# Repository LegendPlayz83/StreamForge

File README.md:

# StreamForge
This is my keyboard design, which I made from scratch in KiCad and Fusion 360

Features:

- 108x Diodes
- 108x keys
- Raspberry Pi Pico
- Customised layout
- KMK firmware
  
### Schematic

### PCB 

### Case

### BOM

| Name | Quantity | Cost | Link |
|------|----------|------|------|
| Akko Creamy Cyan | 108 | $30 | [Buy](https://stackskb.com/store/akko-creamy-cyan-switch-pack-of-45-pre-order/) |
| Durock Smokey Screw-In Stabilizers V2 (4+1 w/ 6.25u spacebar) | 1 | $18.58 | [Buy](https://stackskb.com/store/durock-smokey-screw-in-stabilizers-v2/) |
| Womier Azure Eclipse Side Backlit Cherry PBT Keycap | 1 | $27 | [Buy](https://curiositycaps.in/products/flow-backlit-side-printed-cherry-pbt-keycap-set) |
| Diode 1N4148 Through-Hole | 100 | $2.15 | [Buy](https://www.amazon.in/dp/B084ZP5BJ3) |
| PCB - (Black Color) | 5 | $66 | [Buy](https://order.lioncircuits.com/) |
| Raspberry Pi Pico | 1 | $7.40 | [Buy](https://amzn.in/d/0dd5MeUx) |
| Heatset and Screws | 1 | $0.00 | Amazon |
| Case (top, mid, bot) | 1 | $0.00 | Printing Legion |
| **Total** | | **$151.13** | |

The total costs come out to be $152

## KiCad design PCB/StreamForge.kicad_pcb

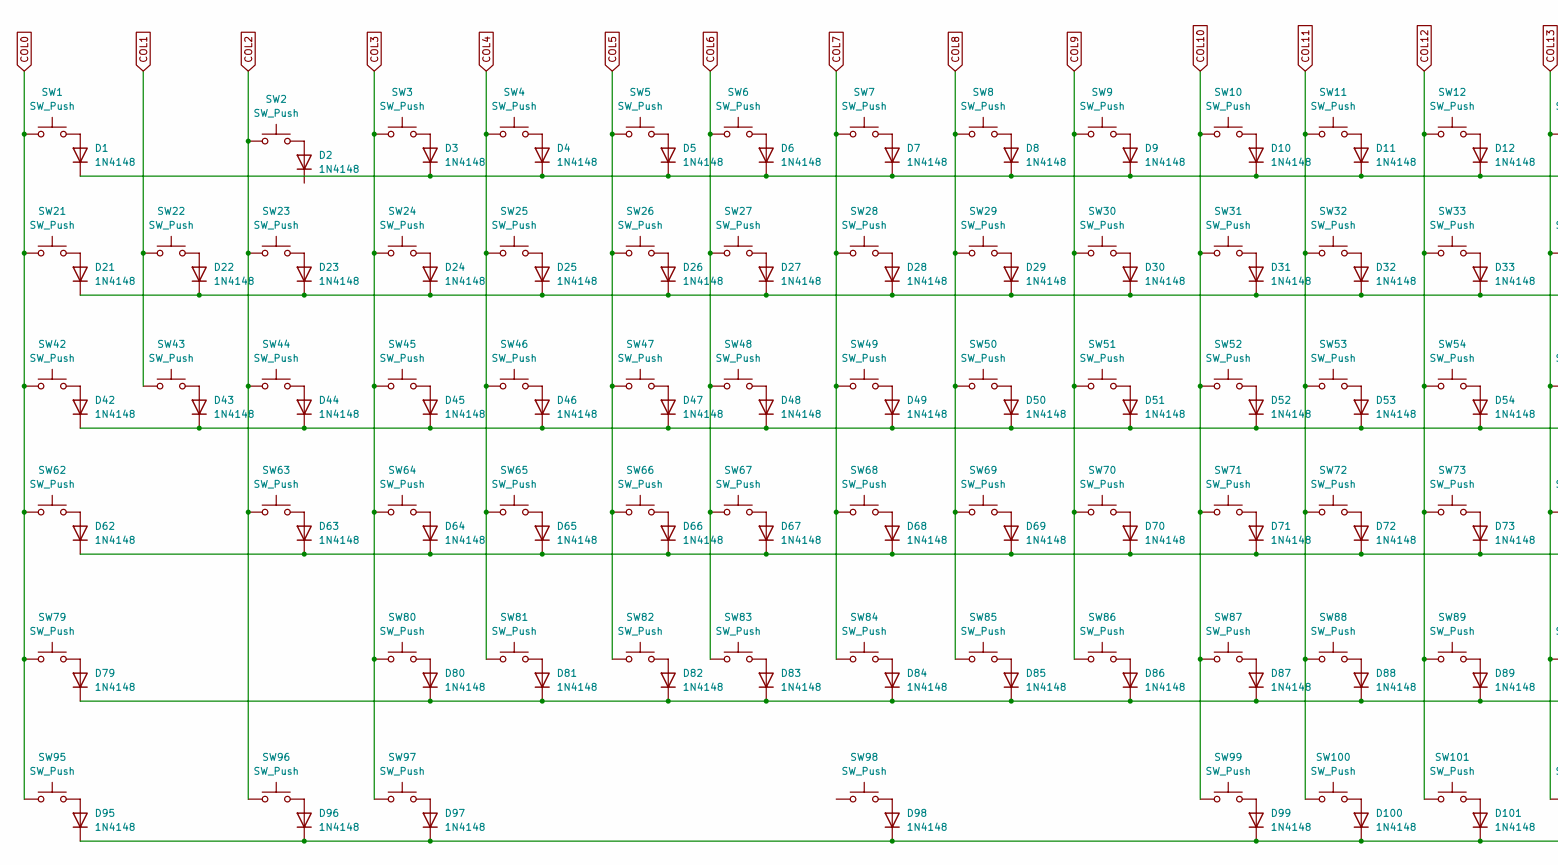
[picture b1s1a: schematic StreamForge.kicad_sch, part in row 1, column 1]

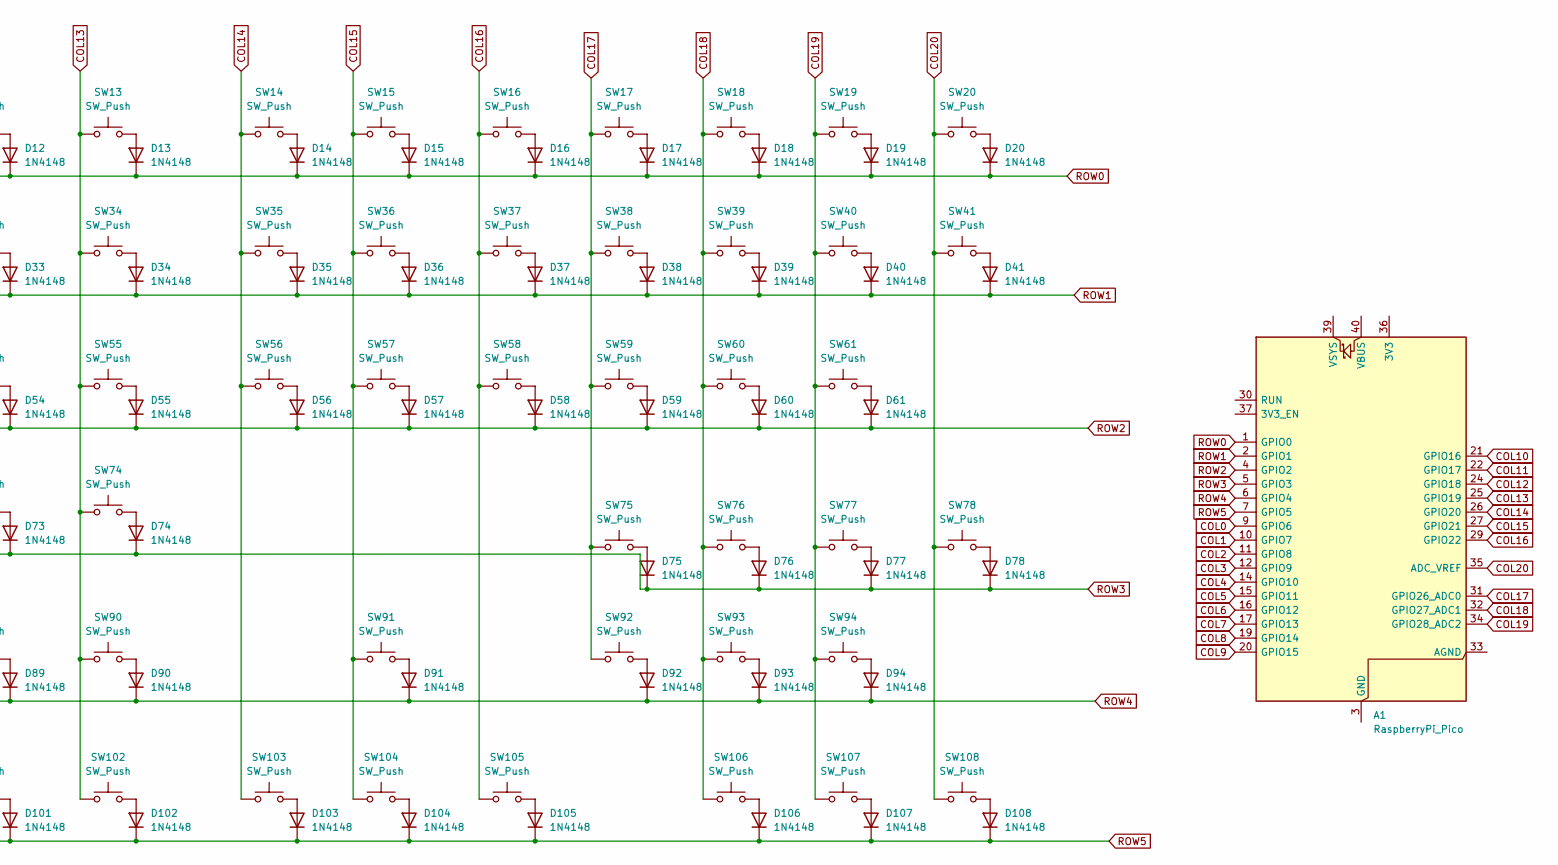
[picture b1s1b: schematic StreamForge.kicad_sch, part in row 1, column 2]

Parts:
A1: RaspberryPi_Pico; RaspberryPi_Pico_Common_THT
D1, D2, D3, D4, D5, D6, D7, D8, D9, D10, D11, D12, D13, D14, D15, D16, D17, D18, D19, D20, D21, D22, D23, D24, D25, D26, D27, D28, D29, D30, D31, D32, D33, D34, D35, D36, D37, D38, D39, D40, D41, D42, D43, D44, D45, D46, D47, D48, D49, D50, D51, D52, D53, D54, D55, D56, D57, D58, D59, D60, D61, D62, D63, D64, D65, D66, D67, D68, D69, D70, D71, D72, D73, D74, D75, D76, D77, D78, D79, D80, D81, D82, D83, D84, D85, D86, D87, D88, D89, D90, D91, D92, D93, D94, D95, D96, D97, D98, D99, D100, D101, D102, D103, D104, D105, D106, D107, D108: 1N4148; D_DO-35_SOD27_P7.62mm_Horizontal
SW1, SW2, SW3, SW4, SW5, SW6, SW7, SW8, SW9, SW10, SW11, SW12, SW13, SW14, SW15, SW16, SW17, SW18, SW19, SW20, SW21, SW22, SW23, SW24, SW25, SW26, SW27, SW28, SW29, SW30, SW31, SW32, SW33, SW35, SW36, SW37, SW38, SW39, SW40, SW41, SW42, SW43, SW44, SW45, SW46, SW47, SW48, SW49, SW50, SW51, SW52, SW53, SW54, SW55, SW56, SW57, SW58, SW59, SW60, SW61, SW62, SW63, SW64, SW65, SW66, SW67, SW68, SW69, SW70, SW71, SW72, SW73, SW75, SW76, SW77, SW79, SW80, SW81, SW82, SW83, SW84, SW85, SW86, SW87, SW88, SW89, SW90, SW91, SW92, SW93, SW94, SW103, SW104, SW105, SW107: SW_Push; SW_Cherry_MX_1.00u_PCB
SW34, SW74, SW106: SW_Push; SW_Cherry_MX_2.00u_PCB
SW78, SW108: SW_Push; SW_Cherry_MX_2.00u_Vertical_PCB
SW95, SW96, SW97, SW99, SW100, SW101, SW102: SW_Push; SW_Cherry_MX_1.25u_PCB
SW98: SW_Push; SW_Cherry_MX_6.25u_PCB

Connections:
COL0: A1.9 (GPIO6), SW1.1, SW21.1, SW42.1, SW62.1, SW79.1, SW95.1
COL1: A1.10 (GPIO7), SW22.1, SW43.1
COL2: A1.11 (GPIO8), SW2.1, SW23.1, SW44.1, SW63.1, SW96.1
COL3: A1.12 (GPIO9), SW3.1, SW24.1, SW45.1, SW64.1, SW80.1, SW97.1
COL4: A1.14 (GPIO10), SW4.1, SW25.1, SW46.1, SW65.1, SW81.1
COL5: A1.15 (GPIO11), SW5.1, SW26.1, SW47.1, SW66.1, SW82.1
COL6: A1.16 (GPIO12), SW6.1, SW27.1, SW48.1, SW67.1, SW83.1
COL7: A1.17 (GPIO13), SW7.1, SW28.1, SW49.1, SW68.1, SW84.1
COL8: A1.19 (GPIO14), SW8.1, SW29.1, SW50.1, SW69.1, SW85.1
COL9: A1.20 (GPIO15), SW9.1, SW30.1, SW51.1, SW70.1, SW86.1
COL10: A1.21 (GPIO16), SW10.1, SW31.1, SW52.1, SW71.1, SW87.1, SW99.1
COL11: A1.22 (GPIO17), SW11.1, SW32.1, SW53.1, SW72.1, SW88.1, SW100.1
COL12: A1.24 (GPIO18), SW12.1, SW33.1, SW54.1, SW73.1, SW89.1, SW101.1
COL13: A1.25 (GPIO19), SW13.1, SW34.1, SW55.1, SW74.1, SW90.1, SW102.1
COL14: A1.26 (GPIO20), SW14.1, SW35.1, SW56.1, SW103.1
COL15: A1.27 (GPIO21), SW15.1, SW36.1, SW57.1, SW91.1, SW104.1
COL16: A1.29 (GPIO22), SW16.1, SW37.1, SW58.1, SW105.1
COL17: A1.31 (GPIO26_ADC0), SW17.1, SW38.1, SW59.1, SW75.1, SW92.1
COL18: A1.32 (GPIO27_ADC1), SW18.1, SW39.1, SW60.1, SW76.1, SW93.1, SW106.1
COL19: A1.34 (GPIO28_ADC2), SW19.1, SW40.1, SW61.1, SW77.1, SW94.1, SW107.1
COL20: A1.35 (ADC_VREF), SW20.1, SW41.1, SW78.1, SW108.1
unnamed: A1.3 (GND), A1.8 (GND), A1.13 (GND), A1.18 (GND), A1.23 (GND), A1.28 (GND), A1.38 (GND)
unnamed: D1.2 (A), SW1.2
unnamed: D2.2 (A), SW2.2
unnamed: D3.2 (A), SW3.2
unnamed: D4.2 (A), SW4.2
unnamed: D5.2 (A), SW5.2
unnamed: D6.2 (A), SW6.2
unnamed: D7.2 (A), SW7.2
unnamed: D8.2 (A), SW8.2
unnamed: D9.2 (A), SW9.2
unnamed: D10.2 (A), SW10.2
unnamed: D11.2 (A), SW11.2
unnamed: D12.2 (A), SW12.2
unnamed: D13.2 (A), SW13.2
unnamed: D14.2 (A), SW14.2
unnamed: D15.2 (A), SW15.2
unnamed: D16.2 (A), SW16.2
unnamed: D17.2 (A), SW17.2
unnamed: D18.2 (A), SW18.2
unnamed: D19.2 (A), SW19.2
unnamed: D20.2 (A), SW20.2
unnamed: D21.2 (A), SW21.2
unnamed: D22.2 (A), SW22.2
unnamed: D23.2 (A), SW23.2
unnamed: D24.2 (A), SW24.2
unnamed: D25.2 (A), SW25.2
unnamed: D26.2 (A), SW26.2
unnamed: D27.2 (A), SW27.2
unnamed: D28.2 (A), SW28.2
unnamed: D29.2 (A), SW29.2
unnamed: D30.2 (A), SW30.2
unnamed: D31.2 (A), SW31.2
unnamed: D32.2 (A), SW32.2
unnamed: D33.2 (A), SW33.2
unnamed: D34.2 (A), SW34.2
unnamed: D35.2 (A), SW35.2
unnamed: D36.2 (A), SW36.2
unnamed: D37.2 (A), SW37.2
unnamed: D38.2 (A), SW38.2
unnamed: D39.2 (A), SW39.2
unnamed: D40.2 (A), SW40.2
unnamed: D41.2 (A), SW41.2
unnamed: D42.2 (A), SW42.2
unnamed: D43.2 (A), SW43.2
unnamed: D44.2 (A), SW44.2
unnamed: D45.2 (A), SW45.2
unnamed: D46.2 (A), SW46.2
unnamed: D47.2 (A), SW47.2
unnamed: D48.2 (A), SW48.2
unnamed: D49.2 (A), SW49.2
unnamed: D50.2 (A), SW50.2
unnamed: D51.2 (A), SW51.2
unnamed: D52.2 (A), SW52.2
unnamed: D53.2 (A), SW53.2
unnamed: D54.2 (A), SW54.2
unnamed: D55.2 (A), SW55.2
unnamed: D56.2 (A), SW56.2
unnamed: D57.2 (A), SW57.2
unnamed: D58.2 (A), SW58.2
unnamed: D59.2 (A), SW59.2
unnamed: D60.2 (A), SW60.2
unnamed: D61.2 (A), SW61.2
unnamed: D62.2 (A), SW62.2
unnamed: D63.2 (A), SW63.2
unnamed: D64.2 (A), SW64.2
unnamed: D65.2 (A), SW65.2
unnamed: D66.2 (A), SW66.2
unnamed: D67.2 (A), SW67.2
unnamed: D68.2 (A), SW68.2
unnamed: D69.2 (A), SW69.2
unnamed: D70.2 (A), SW70.2
unnamed: D71.2 (A), SW71.2
unnamed: D72.2 (A), SW72.2
unnamed: D73.2 (A), SW73.2
unnamed: D74.2 (A), SW74.2
unnamed: D75.2 (A), SW75.2
unnamed: D76.2 (A), SW76.2
unnamed: D77.2 (A), SW77.2
unnamed: D78.2 (A), SW78.2
unnamed: D79.2 (A), SW79.2
unnamed: D80.2 (A), SW80.2
unnamed: D81.2 (A), SW81.2
unnamed: D82.2 (A), SW82.2
unnamed: D83.2 (A), SW83.2
unnamed: D84.2 (A), SW84.2
unnamed: D85.2 (A), SW85.2
unnamed: D86.2 (A), SW86.2
unnamed: D87.2 (A), SW87.2
unnamed: D88.2 (A), SW88.2
unnamed: D89.2 (A), SW89.2
unnamed: D90.2 (A), SW90.2
unnamed: D91.2 (A), SW91.2
unnamed: D92.2 (A), SW92.2
unnamed: D93.2 (A), SW93.2
unnamed: D94.2 (A), SW94.2
unnamed: D95.2 (A), SW95.2
unnamed: D96.2 (A), SW96.2
unnamed: D97.2 (A), SW97.2
unnamed: D98.2 (A), SW98.2
unnamed: D99.2 (A), SW99.2
unnamed: D100.2 (A), SW100.2
unnamed: D101.2 (A), SW101.2
unnamed: D102.2 (A), SW102.2
unnamed: D103.2 (A), SW103.2
unnamed: D104.2 (A), SW104.2
unnamed: D105.2 (A), SW105.2
unnamed: D106.2 (A), SW106.2
unnamed: D107.2 (A), SW107.2
unnamed: D108.2 (A), SW108.2
ROW0: A1.1 (GPIO0), D1.1 (K), D3.1 (K), D4.1 (K), D5.1 (K), D6.1 (K), D7.1 (K), D8.1 (K), D9.1 (K), D10.1 (K), D11.1 (K), D12.1 (K), D13.1 (K), D14.1 (K), D15.1 (K), D16.1 (K), D17.1 (K), D18.1 (K), D19.1 (K), D20.1 (K)
ROW1: A1.2 (GPIO1), D21.1 (K), D22.1 (K), D23.1 (K), D24.1 (K), D25.1 (K), D26.1 (K), D27.1 (K), D28.1 (K), D29.1 (K), D30.1 (K), D31.1 (K), D32.1 (K), D33.1 (K), D34.1 (K), D35.1 (K), D36.1 (K), D37.1 (K), D38.1 (K), D39.1 (K), D40.1 (K), D41.1 (K)
ROW2: A1.4 (GPIO2), D42.1 (K), D43.1 (K), D44.1 (K), D45.1 (K), D46.1 (K), D47.1 (K), D48.1 (K), D49.1 (K), D50.1 (K), D51.1 (K), D52.1 (K), D53.1 (K), D54.1 (K), D55.1 (K), D56.1 (K), D57.1 (K), D58.1 (K), D59.1 (K), D60.1 (K), D61.1 (K)
ROW3: A1.5 (GPIO3), D62.1 (K), D63.1 (K), D64.1 (K), D65.1 (K), D66.1 (K), D67.1 (K), D68.1 (K), D69.1 (K), D70.1 (K), D71.1 (K), D72.1 (K), D73.1 (K), D74.1 (K), D75.1 (K), D76.1 (K), D77.1 (K), D78.1 (K)
ROW4: A1.6 (GPIO4), D79.1 (K), D80.1 (K), D81.1 (K), D82.1 (K), D83.1 (K), D84.1 (K), D85.1 (K), D86.1 (K), D87.1 (K), D88.1 (K), D89.1 (K), D90.1 (K), D91.1 (K), D92.1 (K), D93.1 (K), D94.1 (K)
ROW5: A1.7 (GPIO5), D95.1 (K), D96.1 (K), D97.1 (K), D98.1 (K), D99.1 (K), D100.1 (K), D101.1 (K), D102.1 (K), D103.1 (K), D104.1 (K), D105.1 (K), D106.1 (K), D107.1 (K), D108.1 (K)

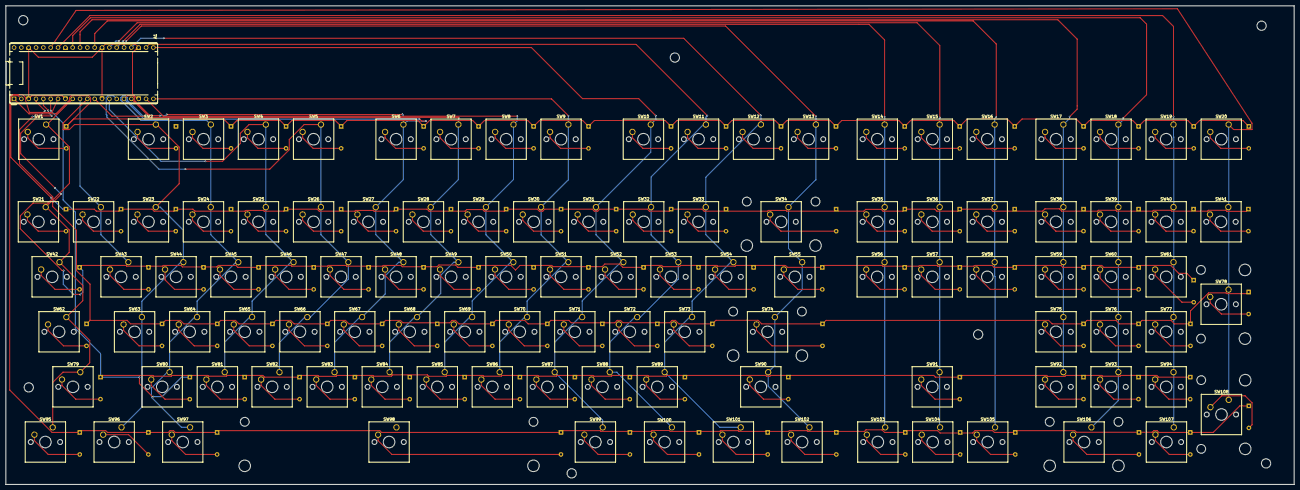
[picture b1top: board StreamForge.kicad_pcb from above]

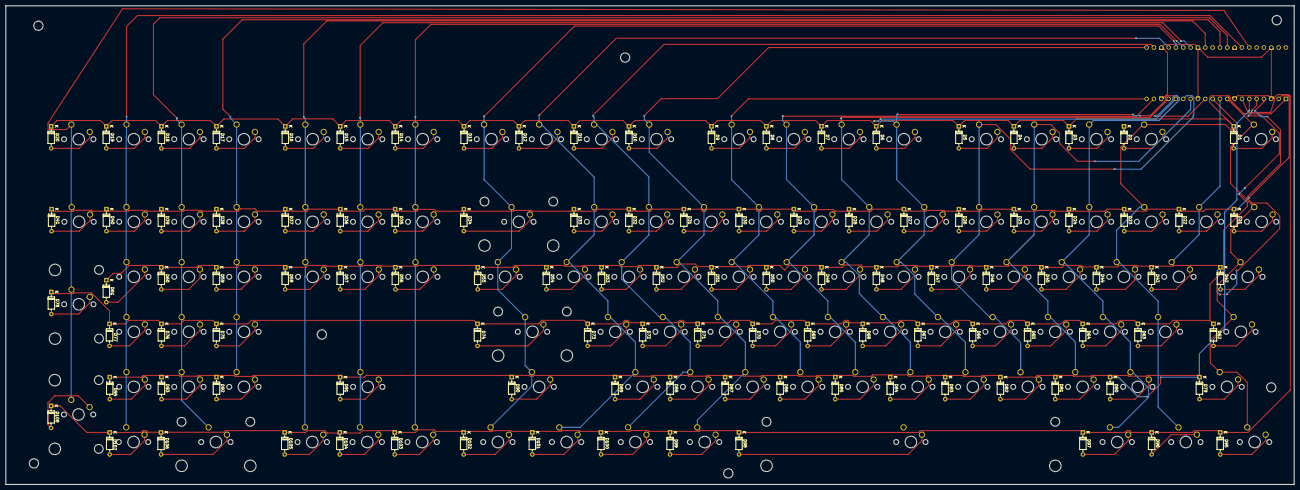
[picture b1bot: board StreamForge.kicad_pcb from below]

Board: 2 copper layers, 446.2 x 165.8 mm, 217 parts (108 on the bottom side), 136 nets.

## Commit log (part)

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2026-06-12 Add entry for firmware writing on 2026-05-05
    Documented the writing of firmware for the keyboard matrix.
